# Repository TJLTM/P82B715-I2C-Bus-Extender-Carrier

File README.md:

# P82B715-I2C-Bus-Extender-Carrier
I2C Bus extender Dev Board

Using the P82B715 chip (NXP Or IT) 
-https://www.nxp.com/docs/en/data-sheet/P82B715.pdf
-https://www.ti.com/lit/ds/symlink/p82b715.pdf?ts=1640486843422

Please reference the data sheet as there will have to be some adjustment for the Pullup resistors for the cable used and distance of the run. I'll do a user manual write up when I get to it.

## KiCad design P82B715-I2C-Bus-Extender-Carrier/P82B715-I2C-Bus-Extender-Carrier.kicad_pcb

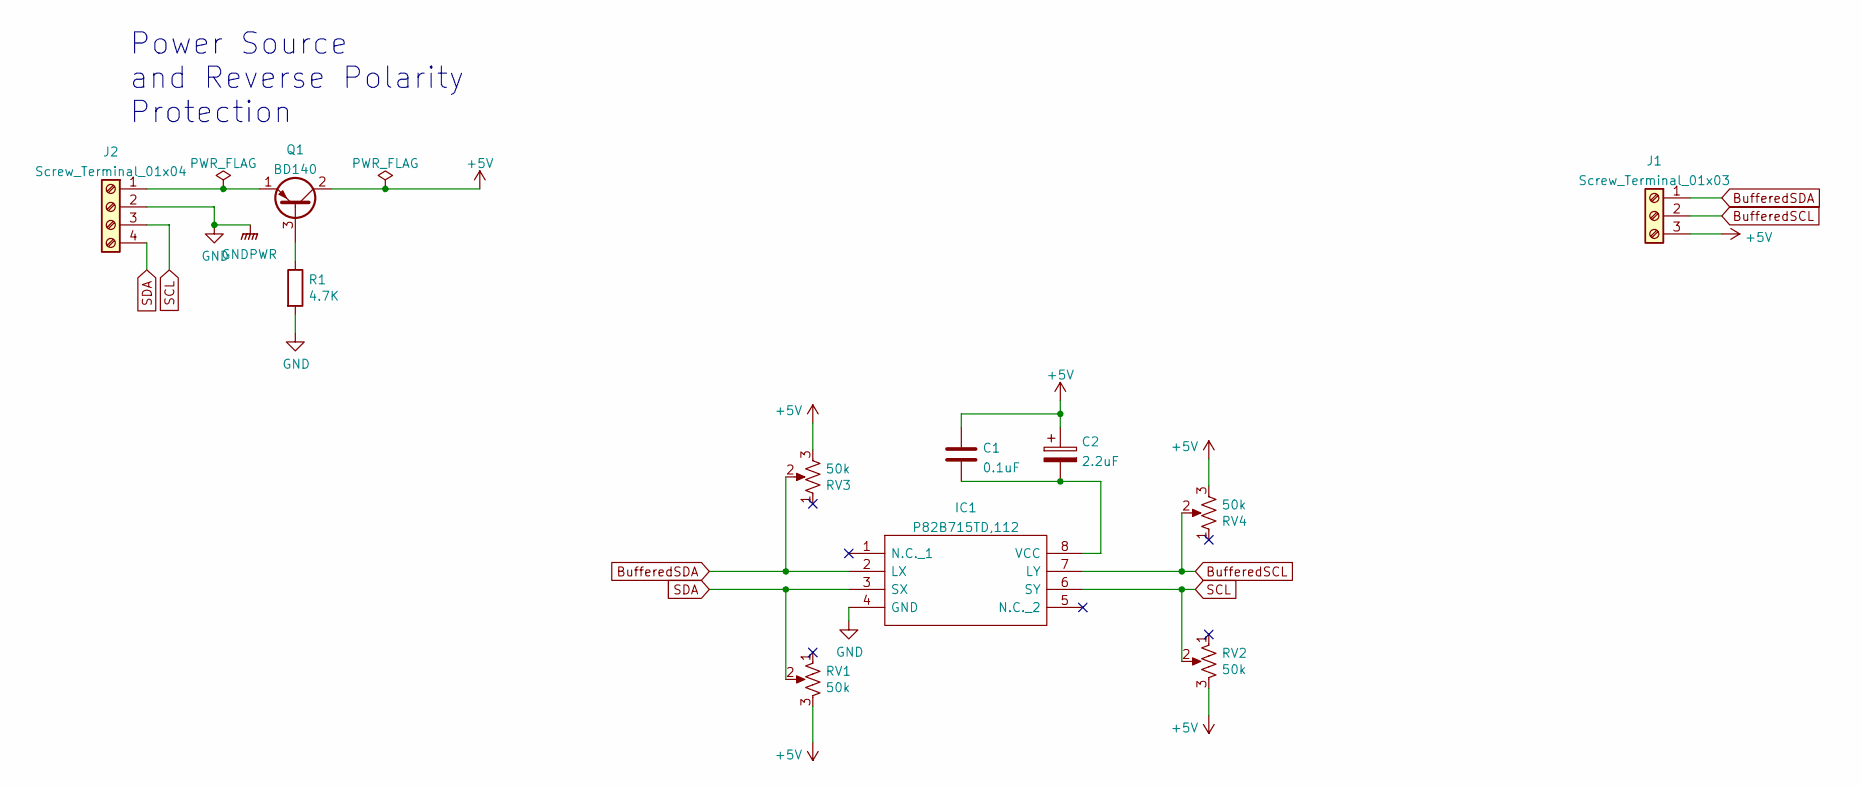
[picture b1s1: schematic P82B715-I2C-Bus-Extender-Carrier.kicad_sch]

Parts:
C1: 0.1uF; C_Rect_L9.0mm_W3.6mm_P7.50mm_MKT
C2: 2.2uF; CP_Radial_D5.0mm_P2.50mm
IC1: P82B715TD,112; SOIC127P600X175-8N; Mouser Part Number 771-P82B715TD
J1: Screw_Terminal_01x03; TerminalBlock_Phoenix_MKDS-1,5-3-5.08_1x03_P5.08mm_Horizont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
J2: Screw_Terminal_01x04; TerminalBlock_Phoenix_MKDS-1,5-4-5.08_1x04_P5.08mm_Horizont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
Q1: BD140; TO-126-3_Vertical
R1: 4.7K; R_Axial_DIN0207_L6.3mm_D2.5mm_P2.54mm_Vertical
RV1, RV2, RV3, RV4: 50k; Potentiometer_Bourns_3296W_Vertical

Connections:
+5V: C1.1, C2.1, J1.3, Q1.2 (C), RV1.3, RV2.3, RV3.3, RV4.3
BufferedSCL: IC1.7 (LY), J1.2, RV4.2
BufferedSDA: IC1.2 (LX), J1.1, RV3.2
GND: IC1.4 (GND), J2.2, R1.2
unnamed: C1.2, C2.2, IC1.8 (VCC)
unnamed: J2.1, Q1.1 (E)
unnamed: Q1.3 (B), R1.1
SCL: IC1.6 (SY), J2.3, RV2.2
SDA: IC1.3 (SX), J2.4, RV1.2

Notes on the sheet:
Power Source and Reverse Polarity Protection

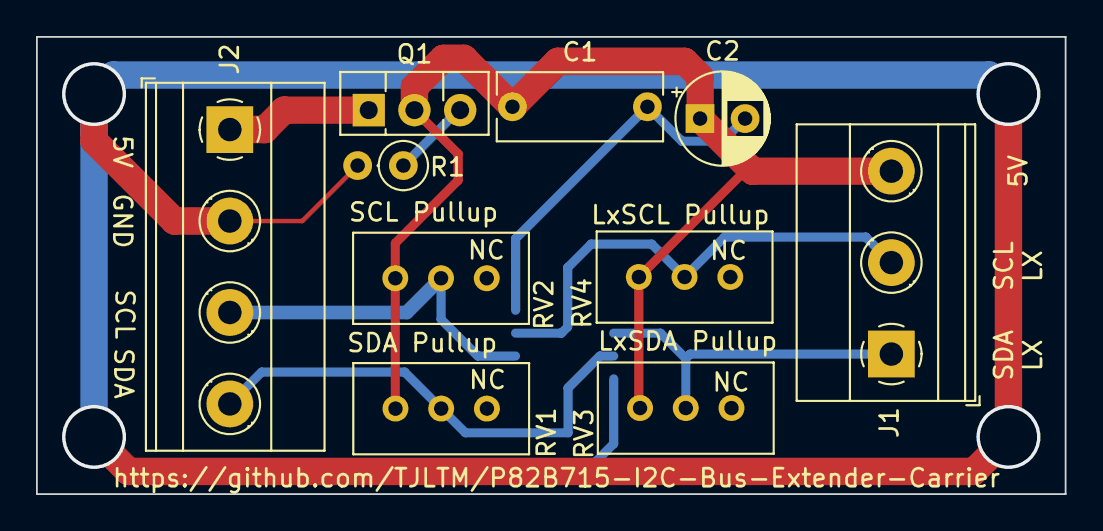
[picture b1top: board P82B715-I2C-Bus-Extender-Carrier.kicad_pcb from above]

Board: 2 copper layers, 57.2 x 25.4 mm, 11 parts (1 on the bottom side), 9 nets.

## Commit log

2022-02-16 initial KiCad schematic and WIP PCB layout.
2022-02-20 routed and laid out. Fab Files included.
